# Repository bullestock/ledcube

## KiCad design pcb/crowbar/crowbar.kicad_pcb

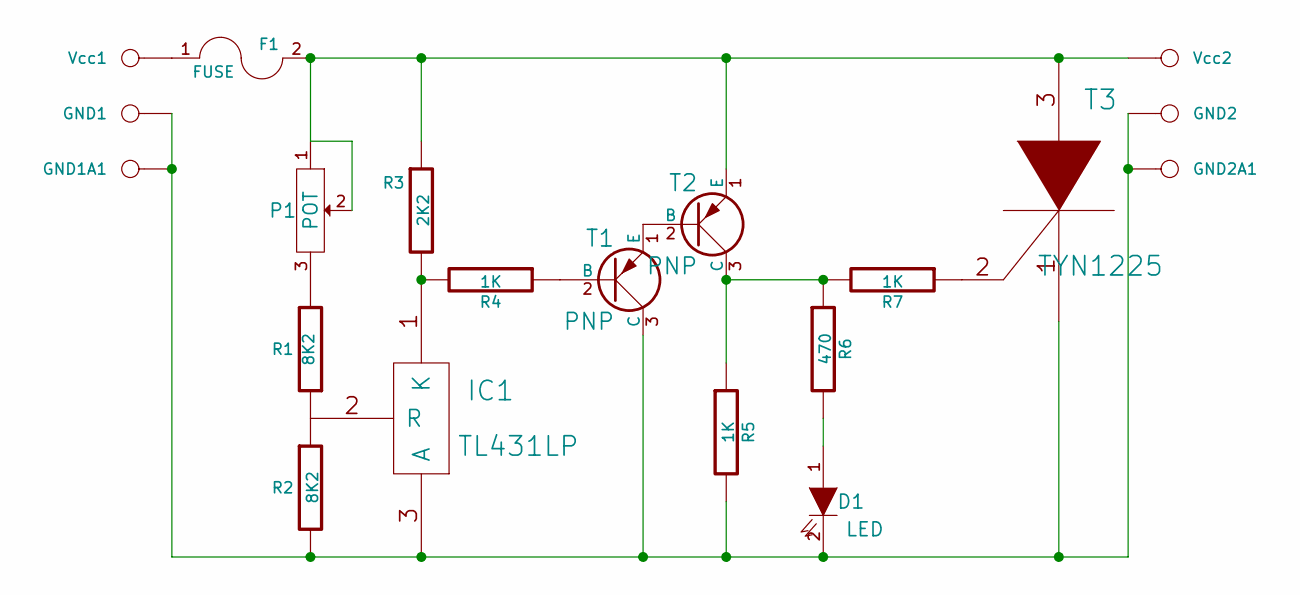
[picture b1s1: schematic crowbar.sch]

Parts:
D1: LED; LED-3MM
F1: FUSE; Fuseholder5x20_horiz_open_universal_Type-III
GND1, GND1A1, GND2, GND2A1: CONN_1; SolderWirePad_single_1-2mmDrill
IC1: TL431LP; TO-92_Molded_Narrow
P1: POT; Potentiometer_Trimmer-Piher-PT15-h2-5_vertical
R1, R2: 8K2; Resistor_Vertical_RM5mm
R3: 2K2; Resistor_Vertical_RM5mm
R4, R5, R7: 1K; Resistor_Vertical_RM5mm
R6: 470; Resistor_Vertical_RM5mm
T1, T2: PNP; TO-92_Molded_Narrow
T3: TYN1225; TO-220_Neutral123_Vertical
Vcc1, Vcc2: CONN_1; SolderWirePad_single_1-2mmDrill

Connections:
unnamed: D1.1 (A), R6.2
unnamed: D1.2 (K), GND1.1, GND1A1.1, GND2.1, GND2A1.1, IC1.3 (A), R2.2, R5.2, T1.3 (C), T3.1 (K)
unnamed: F1.1, Vcc1.1
unnamed: F1.2, P1.1, P1.2, R3.1, T2.1 (E), T3.3 (A), Vcc2.1
unnamed: IC1.1 (K), R3.2, R4.2
unnamed: IC1.2 (R), R1.1, R2.1
unnamed: P1.3, R1.2
unnamed: R4.1, T1.2 (B)
unnamed: R5.1, R6.1, R7.2, T2.3 (C)
unnamed: R7.1, T3.2 (G)
unnamed: T1.1 (E), T2.2 (B)

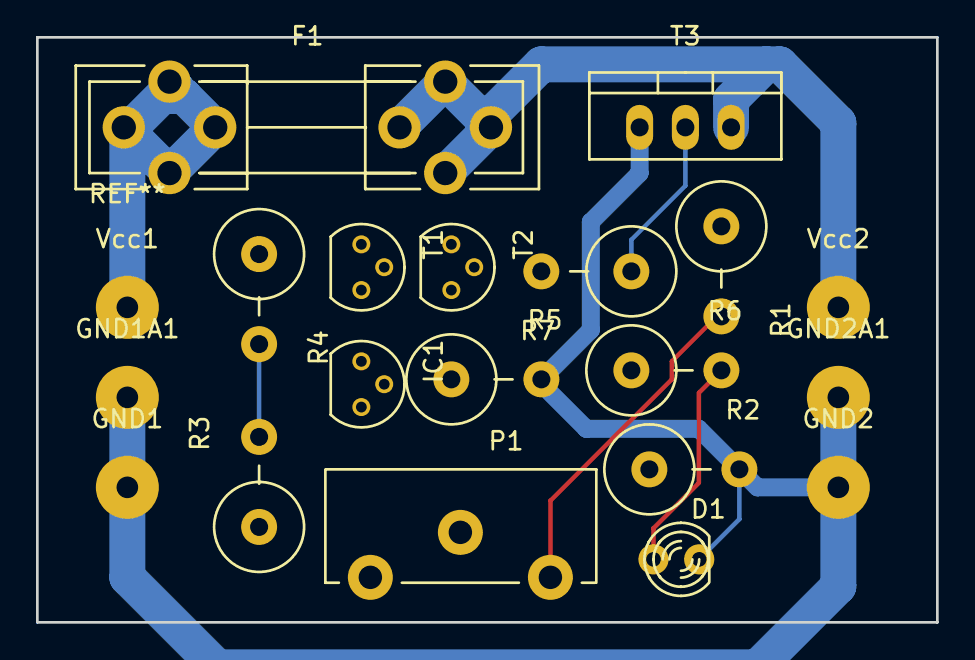
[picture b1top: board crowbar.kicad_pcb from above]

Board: 2 copper layers, 50.0 x 32.5 mm, 20 parts (0 on the bottom side), 11 nets.

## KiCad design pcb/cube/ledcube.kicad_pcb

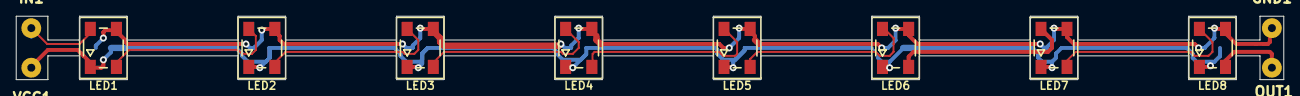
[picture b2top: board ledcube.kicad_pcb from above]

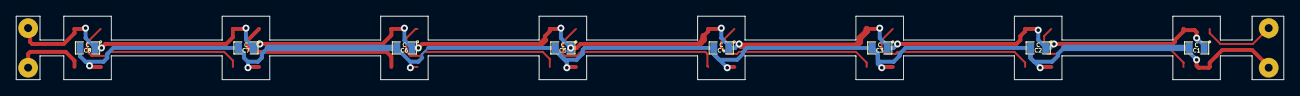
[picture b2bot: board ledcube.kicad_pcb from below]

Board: 2 copper layers, 160.0 x 8.0 mm, 20 parts (8 on the bottom side), 11 nets.

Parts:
C1, C2, C3, C4, C5, C6, C7, C8: C; SMD-0805
GND1: CONN_1; SolderWirePad_single_1mmDrill
IN1: CONN_1; SolderWirePad_single_1mmDrill
LED1, LED2, LED3, LED4, LED5, LED6, LED7, LED8: WS2812B; PLCC4-5050
OUT1: CONN_1; SolderWirePad_single_1mmDrill
VCC1: CONN_1; SolderWirePad_single_1mmDrill

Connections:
unnamed: C1.1, C2.1, C3.1, C4.1, C5.1, C6.1, C7.1, C8.1, GND1.1, LED1.3, LED2.3, LED3.3, LED4.3, LED5.3, LED6.3, LED7.3, LED8.3
unnamed: C1.2, C2.2, C3.2, C4.2, C5.2, C6.2, C7.2, C8.2, LED1.1, LED2.1, LED3.1, LED4.1, LED5.1, LED6.1, LED7.1, LED8.1, VCC1.1
unnamed: IN1.1, LED1.4
unnamed: LED1.2, LED2.4
unnamed: LED2.2, LED3.4
unnamed: LED3.2, LED4.4
unnamed: LED4.2, LED5.4
unnamed: LED5.2, LED6.4
unnamed: LED6.2, LED7.4
unnamed: LED7.2, LED8.4
unnamed: LED8.2, OUT1.1

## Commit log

2014-08-02 First version sent to OSH Park.
2014-09-18 Schematic, components placed.
2015-04-17 Simple rainbow demo.
2015-04-17 Move cube PCB to subfolder, and add crowbar PCB.
2015-07-05 Update PCB.
2015-07-05 Add CM3 libraries. Fix various bugs. Add more modes.
2015-07-05 LibreCAD files.
2015-07-05 Add crowbar PCB.
2015-07-20 Cleanup.
2018-09-08 Add ESP32 skeleton.
2018-09-11 Fix pin number.
2018-09-11 Adapt for cube layout.
2018-09-11 Use BRIGHTNESS from defs.h.
2018-09-11 Add remaining pins.
2018-09-11 Add BRIGHTNESS.
2018-09-11 Reduce overall speed.
2018-09-11 Add more definitions.
2018-09-13 Add stuff.
2018-09-13 Add button handling code.
2018-09-13 Add RowTest animation.
2018-09-15 Ditch FastLED.
2018-09-15 More stuff.
2018-09-15 Implement brightness control.
2018-09-19 Clean up strand definition; move button to a pin with internal pullup.
2018-09-19 Remove unneeded declaration.
2018-09-19 Fix initialization.
2018-09-19 Enable all strands.
2018-09-28 Add support for 3D pixel coordinates.
2018-09-28 First shot.
2018-09-28 Clear when changing program.
2018-09-28 Single snake works.
2018-09-28 Use 5 snakes.
2018-09-28 Enable.
2018-09-29 Expand API.
2018-09-29 Try not to cross other snakes.
2018-09-29 Increase speed.
2018-09-29 Add support for fractional FPS.
2018-09-29 Remove C support.
2018-09-29 Work in progress.
2018-09-30 Add overload.
2018-09-30 Complete character generator.
2018-09-30 Fix bugs.
2018-09-30 Move get_pixel().
2018-09-30 First version.
2018-10-01 Add Block.
2018-10-01 Start Space Invader animation.
2018-10-01 Make number of snakes random.
2018-10-01 Fix bug in button handling.
2018-10-01 Make colours more random.
2018-10-01 Fix size bug.
2018-10-01 Fire at random.
2018-10-02 Fix extent of even-size blocks.
2018-10-02 Add invaders and make them move left and right.
2018-10-03 Fix X axis direction.
2018-10-03 Fix text mirroring.
2018-10-03 Make invaders move correctly.
2018-10-03 Implement hit detection.
